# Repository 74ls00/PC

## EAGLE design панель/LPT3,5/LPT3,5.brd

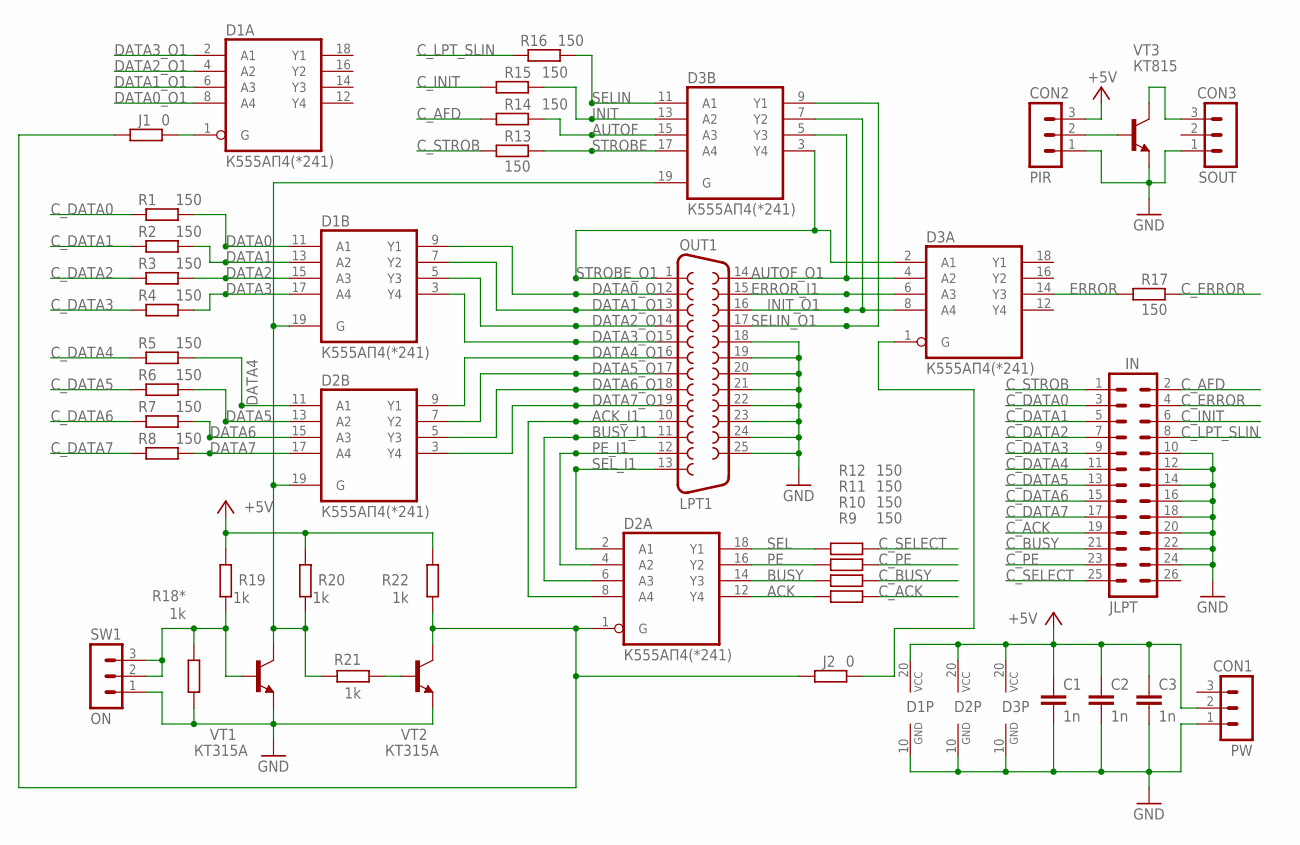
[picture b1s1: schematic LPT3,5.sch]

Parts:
C1, C3: 1n; C050-024X044
C2: 1n; C075-032X103
CON1: PW; MA03-1
CON2: PIR; MA03-1
CON3: SOUT; MA03-1
D1, D2, D3: К555АП4(*241); DIL20
IN: JLPT; MA13-2
J1, J2: 0; R1206
OUT1: LPT1; F25HP
R1, R2, R3, R4, R5, R6, R7, R8, R9, R10, R11, R12: 150; 0204/7
R13, R14, R15, R16, R17: 150; M0805
R18*, R20, R21, R22: 1k; M0805
R19: 1k; M1206
SW1: ON; MA03-1
VT1, VT2: КТ315А; TO92-ECB
VT3: КТ815; TO220BV

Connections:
+5V: C1.1, C2.1, C3.1, CON1.2, CON2.3, D1.20 (VCC), D2.20 (VCC), D3.20 (VCC), R19.2, R20.2, R22.2
ACK: D2.12 (Y4), R9.1
ACK_I1: D2.8 (A4), OUT1.10
AUTOF: D3.15 (A3), R14.2
AUTOF_O1: D3.4 (A2), D3.5 (Y3), OUT1.14
BUSY: D2.14 (Y3), R10.1
BUSY_I1: D2.6 (A3), OUT1.11
C_ACK: IN.19, R9.2
C_AFD: IN.2, R14.1
C_BUSY: IN.21, R10.2
C_DATA0: IN.3, R1.1
C_DATA1: IN.5, R2.1
C_DATA2: IN.7, R3.1
C_DATA3: IN.9, R4.1
C_DATA4: IN.11, R5.1
C_DATA5: IN.13, R6.1
C_DATA6: IN.15, R7.1
C_DATA7: IN.17, R8.1
C_ERROR: IN.4, R17.2
C_INIT: IN.6, R15.1
C_LPT_SLIN: IN.8, R16.1
C_PE: IN.23, R11.2
C_SELECT: IN.25, R12.2
C_STROB: IN.1, R13.1
DATA0: D1.11 (A1), R1.2
DATA0_O1: D1.8 (A4), D1.9 (Y1), OUT1.2
DATA1: D1.13 (A2), R2.2
DATA1_O1: D1.6 (A3), D1.7 (Y2), OUT1.3
DATA2: D1.15 (A3), R3.2
DATA2_O1: D1.4 (A2), D1.5 (Y3), OUT1.4
DATA3: D1.17 (A4), R4.2
DATA3_O1: D1.2 (A1), D1.3 (Y4), OUT1.5
DATA4: D2.11 (A1), R5.2
DATA4_O1: D2.9 (Y1), OUT1.6
DATA5: D2.13 (A2), R6.2
DATA5_O1: D2.7 (Y2), OUT1.7
DATA6: D2.15 (A3), R7.2
DATA6_O1: D2.5 (Y3), OUT1.8
DATA7: D2.17 (A4), R8.2
DATA7_O1: D2.3 (Y4), OUT1.9
ERROR: D3.14 (Y3), R17.1
ERROR_I1: D3.6 (A3), OUT1.15
GND: C1.2, C2.2, C3.2, CON1.1, CON2.1, CON3.1, D1.10 (GND), D2.10 (GND), D3.10 (GND), IN.10, IN.12, IN.14, IN.16, IN.18, IN.20, IN.22, IN.24, OUT1.18, OUT1.19, OUT1.20, OUT1.21, OUT1.22, OUT1.23, OUT1.24, OUT1.25, R18*.1, SW1.1, VT1.E, VT2.E, VT3.3 (E)
INIT: D3.13 (A2), R15.2
INIT_O1: D3.7 (Y2), D3.8 (A4), OUT1.16
unnamed: D1.19 (G), D2.19 (G), D3.19 (G), R20.1, R21.2, VT1.C
unnamed: CON2.2, VT3.1 (B)
unnamed: D2.1 (G), J1.1, J2.1, R22.1, VT2.C
unnamed: D1.1 (G), J1.2
unnamed: R18*.2, R19.1, SW1.2, SW1.3, VT1.B
unnamed: D3.1 (G), J2.2
unnamed: CON3.3, VT3.2 (C)
unnamed: R21.1, VT2.B
PE: D2.16 (Y2), R11.1
PE_I1: D2.4 (A2), OUT1.12
SEL: D2.18 (Y1), R12.1
SELIN: D3.11 (A1), R16.2
SELIN_O1: D3.9 (Y1), OUT1.17
SEL_I1: D2.2 (A1), OUT1.13
STROBE: D3.17 (A4), R13.2
STROBE_O1: D3.2 (A1), D3.3 (Y4), OUT1.1

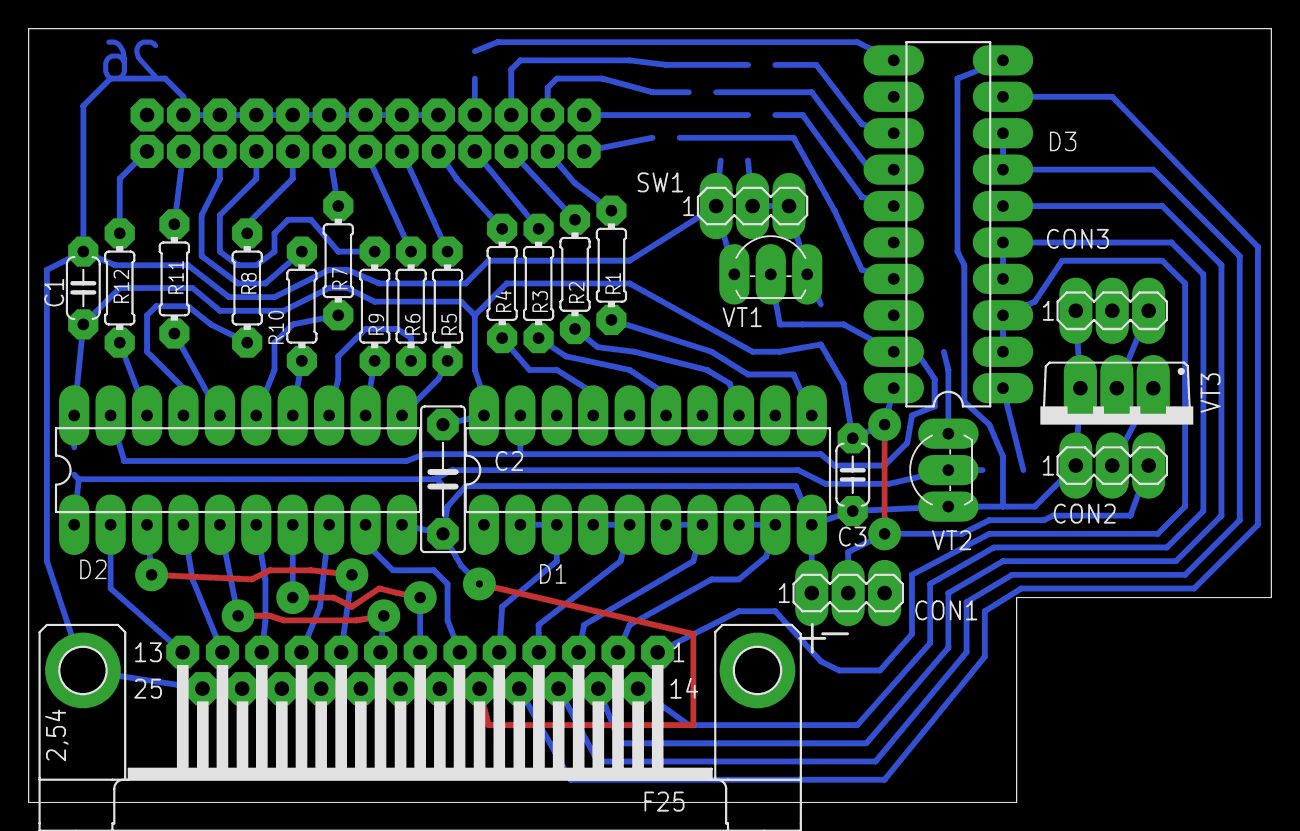
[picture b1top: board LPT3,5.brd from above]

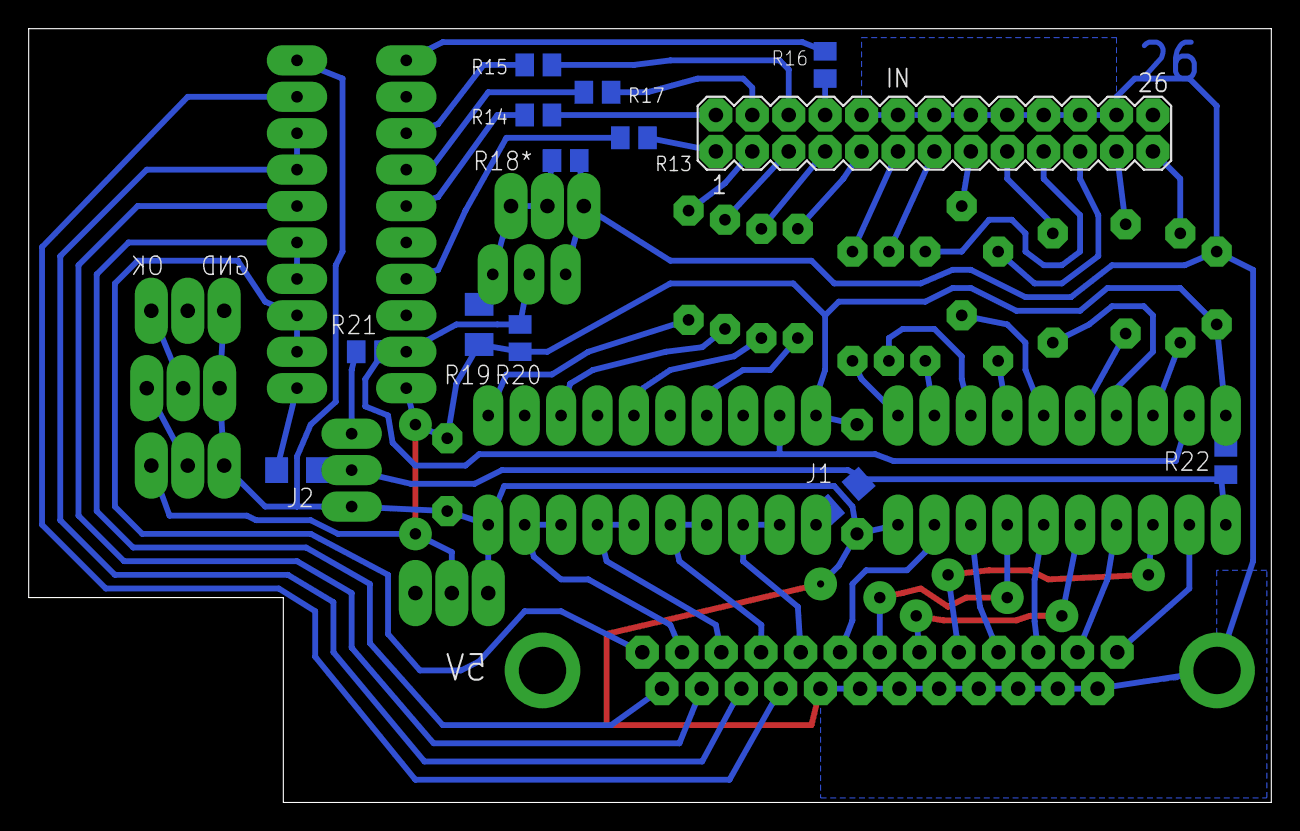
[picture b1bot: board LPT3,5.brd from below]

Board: 2 copper layers, 86.7 x 54.0 mm, 39 parts (13 on the bottom side), 61 nets.

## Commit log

2016-12-19 add rm
2016-12-22 clear pcb
2016-12-23 clear
2018-11-27 add pin cabl
